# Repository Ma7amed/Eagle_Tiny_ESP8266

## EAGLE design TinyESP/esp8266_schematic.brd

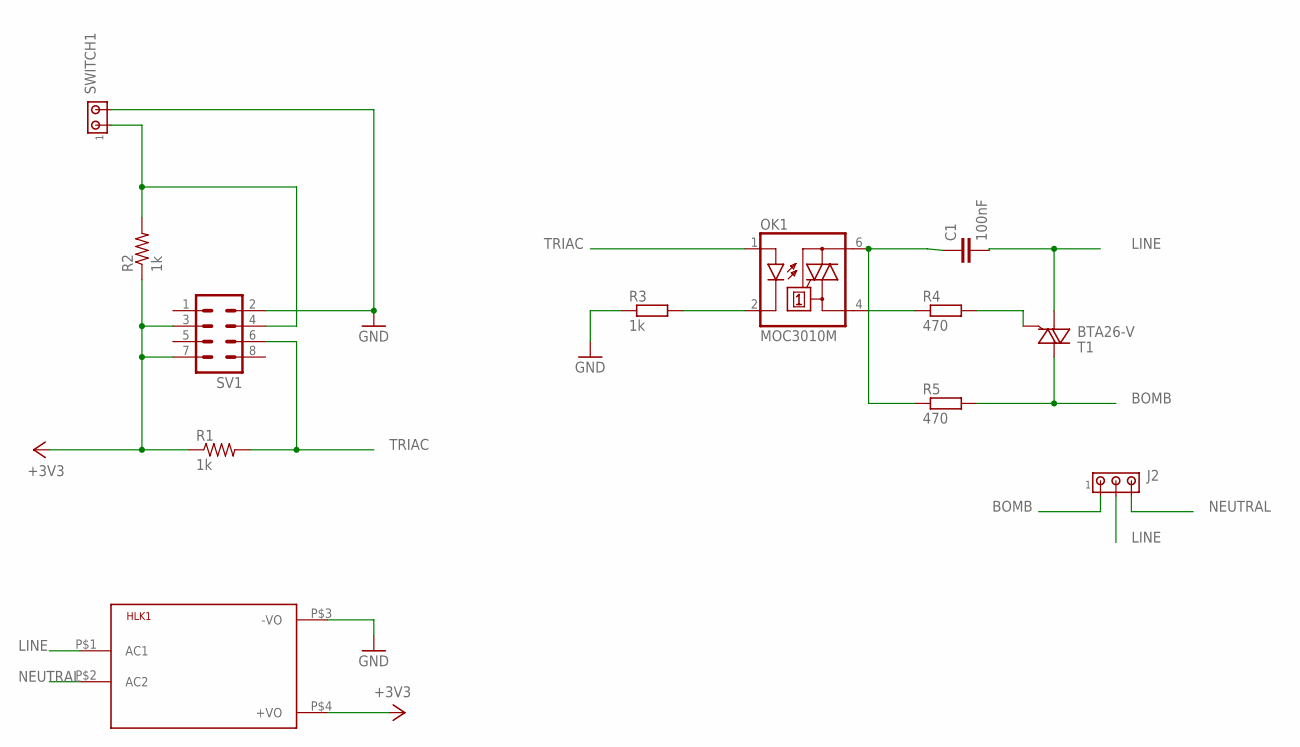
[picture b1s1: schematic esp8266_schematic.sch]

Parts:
C1: 100nF; C102-043X133
HLK1: HLK-PM013W; HLK-PM01
J2: MTA03-100; 10X03MTA
OK1: MOC3010M; DIL06
R1, R2: 1k; 0207/2V
R3: 1k; 0204/5
R4, R5: 470; 0207/15
SV1: MA04-2
SWITCH1: MTA02-100; 10X02MTA
T1: BTA26-V; TOP3S-1

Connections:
+3V3: HLK1.P$4 (+VO), R1.1, R2.1, SV1.3, SV1.7
BOMB: J2.1, R5.2, T1.A2
GND: HLK1.P$3 (-VO), R3.1, SV1.2, SWITCH1.2
LINE: C1.2, HLK1.P$1 (AC1), J2.2, T1.A1
unnamed: OK1.2 (C), R3.2
unnamed: R2.2, SV1.4, SWITCH1.1
unnamed: C1.1, OK1.6 (A2), R5.1
unnamed: OK1.4 (A1), R4.1
unnamed: R4.2, T1.G
NEUTRAL: HLK1.P$2 (AC2), J2.3
TRIAC: OK1.1 (A), R1.2, SV1.6

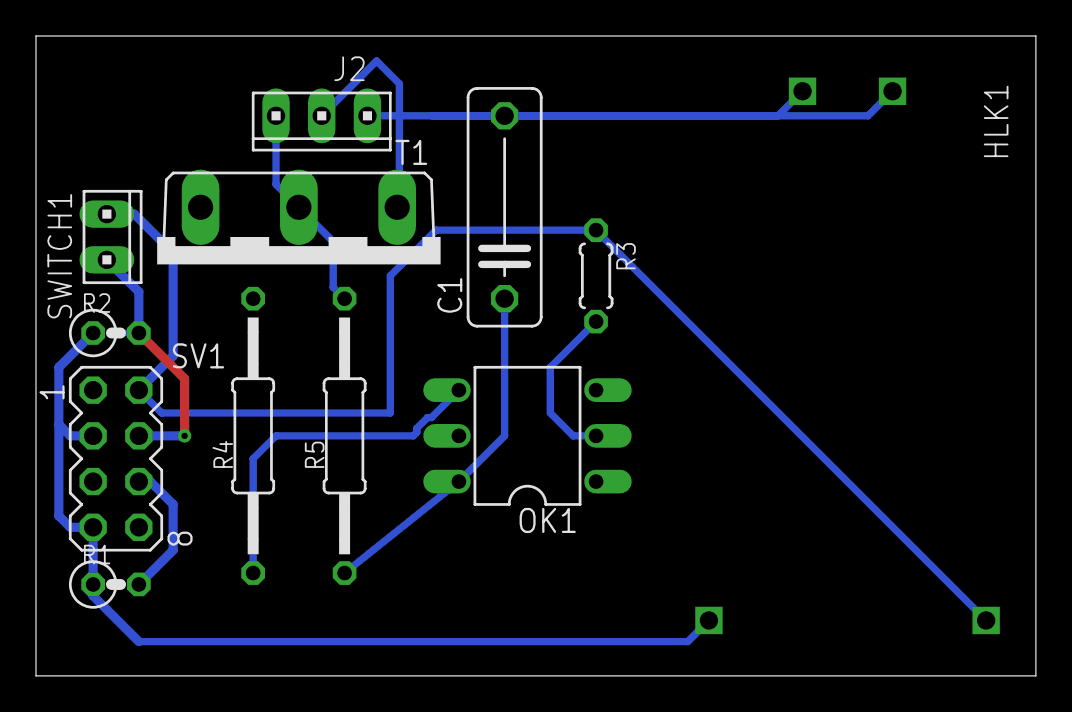
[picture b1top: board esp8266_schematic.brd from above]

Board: 2 copper layers, 55.5 x 35.6 mm, 12 parts (0 on the bottom side), 11 nets.

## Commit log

2019-08-16 init
